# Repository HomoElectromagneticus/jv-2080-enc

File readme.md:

This PCBA design implements a replacement for the main "value" encoder on the Roland JV-2080 synthesizer. This is useful because the original part is no longer manufactured.

In short, this design leverages work available on mitxela.com, namely: https://mitxela.com/projects/jv1080_encoder_repair. The code shown on that page creates an elegant low-power interface between a standard rotary encoder commonly available at the time of this writing and what the JV-2080 expects. I encourage any reader here to explore that page to learn more.

You may find the necessary files to build this project for yourself on the "Releases" section of this repository page. Note that you will also need the pre-compiled binary to flash onto the ATTiny13A as well as a means to flash it. You may find the pre-compiled binary here: https://github.com/mitxela/jv1080-encoder. Pay attention to the fuse settings required for the microcontroller: 
  - high fuse byte -> 0xFF 
  - low fuse -> 0x73

These will need to be set when flashing the ATTiny13A.

For more information about the process, please visit https://homoelectromagneticus.com/projects/jv_2080_enc.php. If you try this project for yourself and run into a problem, do not hesitate to create an issue in this repository and I will do my best to help you.

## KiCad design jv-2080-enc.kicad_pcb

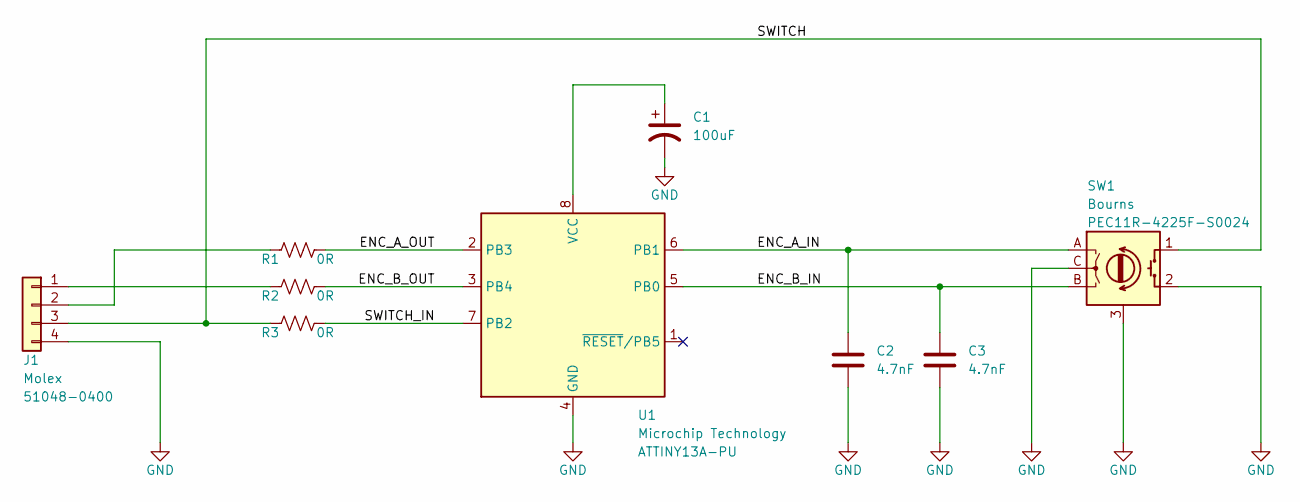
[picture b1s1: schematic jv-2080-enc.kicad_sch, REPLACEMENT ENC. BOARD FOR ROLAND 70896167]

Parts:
C1: 100uF; CP_Radial_D5.0mm_P2.00mm; Manuf PN UVY1E101MDD
C2, C3: 4.7nF; C_Rect_L7.0mm_W2.0mm_P5.00mm; Manuf PN R82EC1470AA50K
J1: Conn_01x04; Molex_51048-0400; Manuf PN 51048-0400
R1, R2, R3: 0R; R_Axial_DIN0207_L6.3mm_D2.5mm_P7.62mm_Horizontal
SW1: RotaryEncoder_Switch; Rotary_Encoder_Switched_PEC11R; Manuf PN PEC11R-4225F-S0024
U1: ATtiny13A-P; DIP-8_W7.62mm; Manuf PN ATTINY13A-PU

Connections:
/ENC_A_IN: C2.1, SW1.A, U1.6 (PB1)
/ENC_A_OUT: R1.2, U1.2 (PB3)
/ENC_B_IN: C3.1, SW1.B, U1.5 (PB0)
/ENC_B_OUT: R2.2, U1.3 (PB4)
/SWITCH: J1.3, R3.1, SW1.1 (S1)
/SWITCH_IN: R3.2, U1.7 (PB2)
GND: C1.2, C2.2, C3.2, J1.4, SW1.2 (S2), SW1.3 (Chassis), SW1.C, U1.4 (GND)
unnamed: C1.1, U1.8 (VCC)
unnamed: J1.1, R2.1
unnamed: J1.2, R1.1

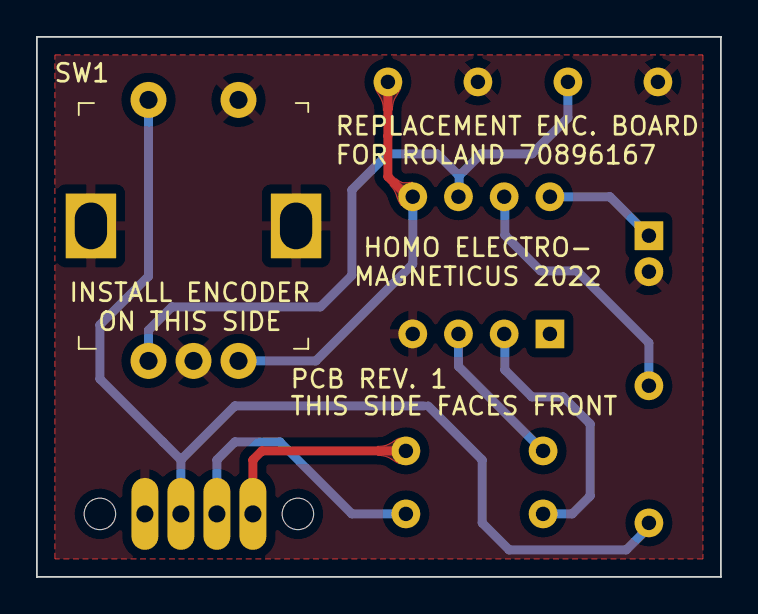
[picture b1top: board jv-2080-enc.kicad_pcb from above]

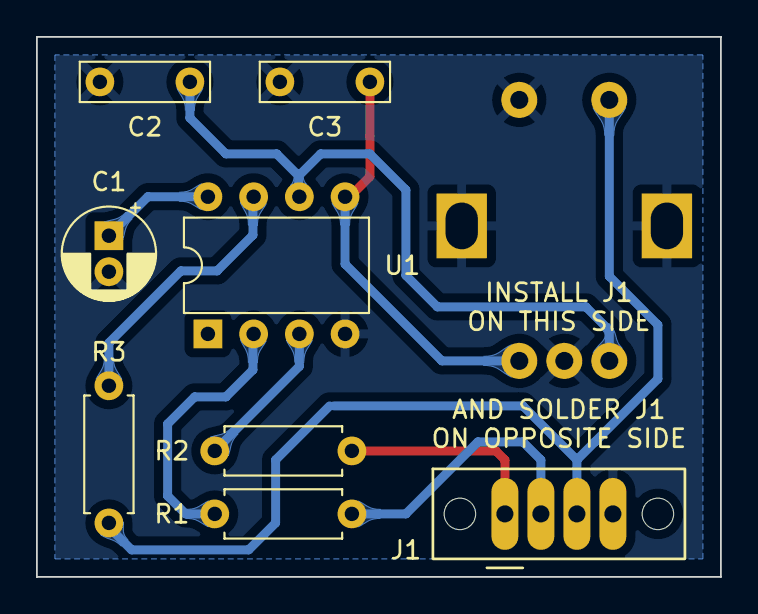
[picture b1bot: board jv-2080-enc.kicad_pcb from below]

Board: 2 copper layers, 38.0 x 30.0 mm, 9 parts (8 on the bottom side), 10 nets.

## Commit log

2022-04-09 initial commit of ignore file
2022-04-09 initial commit of KiCAD design
2022-04-09 Adding empty markdown readme file for now
2022-04-10 Filled out the basic details of a readme
2022-04-10 Added CC0 license
2022-04-10 Hiding mac system files from the repo
2022-04-10 Rounding all the tracks and adding teardrops for fun.
2022-04-10 fixed typos in the readme
2022-04-10 Moved most of the components to the other side of the PCBA to account for the much smaller body size of a modern encoder vs the original one.
2022-04-20 Re-drew the schematic to be easier to read. Tweaked the layout so that the PCB is 2mm less wide.
2022-04-21 Further schematic and layout tweaks - minor stuff
2022-04-21 Tweaked output settings to build gerbers and drills the right way.
2022-05-26 Fixed miswired encoder connection. Added helpful silkscreen text. Bumped revision number from 0 to 1.
2022-05-26 Removed unused round tracks configuration
2022-05-26 Added gerber files for production
2022-06-11 Added manufacturer and part number details to necessary circuit elements.
2022-06-12 Corrected part number of the rotary encoder
2022-06-12 Updated readme with more helpful information
2022-06-12 Added info about microcontroller fuse settings
